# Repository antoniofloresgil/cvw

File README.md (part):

# core-v-wally

This repository is a fork of [openhwgroup/cvw](https://github.com/openhwgroup/cvw) (CORE-V-Wally) that is
more than Wally: next to the processor it holds an [open FPGA flow, an open ASIC flow with a
microcontroller chip, a KiCad test board and FreeRTOS](#what-this-fork-adds). The core and its configurations
are Wally's, upstream is merged into `main` regularly, and every addition to the core is behind a configuration
parameter that is off by default, so the upstream configurations behave as before
([the inventory](docs/engineering/upstream-coupling.md)). The rest of this README is upstream's setup guide
and still applies.

Wally is a 5-stage pipelined processor configurable to support up through the RVA22 profile, including virtual memory, PMP, and the various privileged modes and CSRs. The rv64gc configuration supports:

- RV64IMAFDCB with M, S, and U modes
- Zicsr, Zifencei, Zicntr, Zihpm, Zicond, and Zicclsm
- Zbc
- Zkn scalar crypto (Zbkb, Zbkc, Zbkx, Zknd, Zkne, and Zknh)
- Zcb
- Zfh and Zfa
- Zicbom, Zicboz, and Zicbop
- Sstc
- Sv39, Sv48, and Sv57 virtual memory with Svpbmt, Svnapot, Svinval, and Svadu
- 16 PMP entries

Other configurations range down to a minimal RV32E core, and derivative configurations add the Q extension. Wally provides optional caches, branch prediction, and standard RISC-V peripherals (CLINT, PLIC, UART, GPIO).   Wally is written in SystemVerilog.  It passes the [RISC-V Arch Tests](https://github.com/riscv/riscv-arch-test) and boots Linux on an FPGA.  Wally is part of the OpenHW Foundation family of robust open RISC-V cores.

Wally is described in a textbook, [*RISC-V System-on-Chip Design*](https://pages.hmc.edu/harris/ddca/rvsocd.html), by Harris, Stine, Thompson, and Harris.  Users should follow the setup instructions below.

# What this fork adds

| | What it is | Where |
|---|---|---|
| **Open FPGA flow** | Wally on Xilinx 7-series boards with no Vivado: Yosys, nextpnr-xilinx (openXC7) and Project X-Ray, with LiteX/LiteDRAM for the DDR3 instead of Vivado's MIG. On the Nexys Video the RV32 design runs at 40 MHz and RV64GC boots Linux to a BusyBox shell at 12.5 MHz. The Vivado flow stays. The chip below also builds for the Nexys Video (`make nexysvideochip`). | `fpga/`, [flow and LiteDRAM](docs/fpga-opensource-litedram.md), [DDR3 bring-up](docs/engineering/experiments/open-ddr3-bringup.md), [the chip on the FPGA](docs/fpga-chip.md) |
| **Open ASIC flow** | Wally from RTL to GDS with LibreLane on the IHP SG13G2 and SG13CMOS5L open PDKs, with KLayout and Magic DRC, LVS and timing signoff, all open tools. It builds a chip: **`asic_soc_rv32imac`**, an RV32IMAC RISC-V microcontroller with 16 PMP entries, the JTAG debug port and instruction trace, 64 KiB of SRAM in eight macros, an SPI-flash/UART bootloader, a timer with PWM and capture, a watchdog, I2C, an RTC and a pad ring for a QFN 32. It has not been fabricated. | `asic/librelane/`, [README](asic/librelane/README.md), [ADR 0022](docs/engineering/decisions/0022-asic-microcontroller.md) |
| **Test board** | A KiCad 10 board for that chip: USB-C, an FT2232H for JTAG and UART, SPI flash, I2C and analog parts to try the peripherals, and, in a second variant (rev A-S), a test socket for the QFN 32 chip next to the direct-soldering one (rev A). Its schematic and PCB are generated and routed by Python scripts, and `fab.py` writes the JLCPCB files. `make boardsim` simulates the chip on the board's own netlist. | `hardware/board/`, [README](hardware/board/README.md), [ADR 0023](docs/engineering/decisions/0023-mcu-test-board.md) |
| **Real-time OS** | FreeRTOS and Zephyr run on the chip, with static memory protection from locked PMP entries (FreeRTOS) and User-mode threads isolated by the PMP (Zephyr, with drivers for the UART, GPIO, SPI, PWM, I2C, watchdog, MCU timer with capture and RTC, GPIO and I2C interrupts, and the instruction trace switched on by the kernel); their demos are tested in the chip's RTL simulation (`make chipsim`, 15 tests). | `asic/librelane/chip/freertos/`, `asic/librelane/chip/zephyr/` |
| **Debug and trace** | RISC-V Debug 1.0 over JTAG (halt, step, triggers, System Bus Access; OpenOCD and GDB) and an E-Trace instruction trace. | [debug](docs/debug.md), [trace](docs/trace.md), `testbench/debug/` |
| **Multicore and PMU** | Optional multicore (`NCORES`) with private MSI/MESI caches and Linux SMP; the Sscofpmf, Smcntrpmf and Smcdeleg counter extensions and an SBI PMU. | [engineering notes](docs/engineering/README.md) |

The design decisions, measurements and what is still open are written down in
[`docs/engineering/`](docs/engineering/README.md): architecture decision records, experiment records and
[current work](docs/engineering/current-work.md). To use the fork, clone `antoniofloresgil/cvw` with
`--recurse-submodules` (the step-by-step setup below clones upstream; the commands are the same).

# Configurations

Wally default configurations are listed below.  Synthesis results are from TSMC 28HPC+ TT conditions (0.9 V, 25 °C), Design Compiler Y-2026.03-SP3 physical (topographical) synthesis, with timing that includes its estimated wire delays, before place and route.  The hierarchy is ungrouped automatically, and the clock frequency counts paths into the register files, which are written on the falling edge, as half-cycle paths.  Embench results are without F and D.

|                       | rv32e             | rv32i               | rv32imc                           | rv32imcb                              | rv32gc                                                                                                                                       | rv64i      | rv64gc                                                                                                                                                                    |
| --------------------- | ----------------- | ------------------- | --------------------------------- | ------------------------------------- | -------------------------------------------------------------------------------------------------------------------------------------------- | ---------- | ------------------------------------------------------------------------------------------------------------------------------------------------------------------------- |
| Features              | Tiny Embedded     | RVI20U32            | Microcontroller                   | Microcontroller with bit manipulation | Like rv64gc                                                                                                                                  | RVI20U64   | RVA22S64                                                                                                                                                                  |
| Privilege Modes       | M                 | M                   | M, U                              | M, U                                  | M, S, U                                                                                                                                      | M          | M, S, U                                                                                                                                                                   |
| Extensions            | E                 | I                   | IMC, Zicsr, Zicntr, Zihpm         | IMCB, Zbc, Zicsr, Zicntr, Zihpm       | IMAFDCB, Zbc, Zbkb, Zbkc, Zbkx, Zkn, Zkt, Zfh, Zfa, Zcb, Zicond, Zicbom, Zicboz, Zicbop, Zifencei, Zicntr, Zihpm, Sv32, Svadu, Svinval, Sstc | I          | IMAFDCB, Zbc, Zbkb, Zbkc, Zbkx, Zkn, Zkt, Zfh, Zfa, Zcb, Zicond, Zicbom, Zicboz, Zicbop, Zifencei, Zicntr, Zihpm, Sv39, Sv48, Sv57, Svadu, Svinval, Svnapot, Svpbmt, Sstc |
| Memory                | Bus               | IROM, DTIM          | IROM, DTIM                        | IROM, DTIM                            | 16 KB I$, 16 KB D$                                                                                                                           | IROM, DTIM | 16 KB I$, 16 KB D$                                                                                                                                                        |
| Branch Predictor      | None              | None                | Static (backward taken)           | Static (backward taken)               | 1K gshare, 1K BTB, 16 RAS                                                                                                                    | None       | 1K gshare, 1K BTB, 16 RAS                                                                                                                                                 |
| Peripherals           | No                | No                  | CLINT, PLIC, UART, GPIO, SPI, PWM | CLINT, PLIC, UART, GPIO, SPI, PWM     | CLINT, PLIC, UART, GPIO, SPI, PWM                                                                                                            | No         | CLINT, PLIC, UART, GPIO, SPI, PWM                                                                                                                                         |
| External bus (AHB)    | Yes               | No                  | Yes                               | Yes                                   | Yes                                                                                                                                          | No         | Yes                                                                                                                                                                       |
| CoreMark/MHz          | 0.35              | 1.04                | 3.54                              | 4.06                                  | 4.33                                                                                                                                         | 0.91       | 4.20                                                                                                                                                                      |
| Embench Speed         | 0.20              | 0.63                | 1.58                              | 1.65                                  | 1.70                                                                                                                                         | 0.70       | 2.03                                                                                                                                                                      |
| Clock Frequency (MHz) | 2800              | 2780                | 1880                              | 1890                                  | 920                                                                                                                                          | 2540       | 770                                                                                                                                                                       |
| Total Area (mm^2)     | 0.0058            | 0.0065              | 0.020                             | 0.021                                 | 0.43                                                                                                                                         | 0.016      | 0.48                                                                                                                                                                      |
| Logic Area (mm^2)     | 0.0058            | 0.0065              | 0.020                             | 0.021                                 | 0.11                                                                                                                                         | 0.016      | 0.17                                                                                                                                                                      |
| Flip-Flops            | 573 + 495 latches | 573 + 1,023 latches | 1,792 + 1,023 latches             | 1,801 + 1,023 latches                 | 16,496                                                                                                                                       | 3,026      | 24,416                                                                                                                                                                    |
| Gates                 | 3,650             | 4,495               | 14,583                            | 16,122                                | 89,945                                                                                                                                       | 10,309     | 139,072                                                                                                                                                                   |
| RAM Bits              | 0                 | 0                   | 0                                 | 0                                     | 312,320                                                                                                                                      | 0          | 356,352                                                                                                                                                                   |

CoreMark and Embench (speed-optimized, scored per MHz) are compiled for each configuration's ISA and simulated with Verilator.  With F and D, the compiler optimizes away much of the timed work in the Embench nbody, st, and minver benchmarks, so Embench is compiled without F and D for every configuration, and its floating-point benchmarks use software floating point rather than the FPU.  rv32e, rv32i, and rv64i add performance counters to time the benchmarks.  Synthesis is of `wallypipelinedcore`, with rv32i, rv32imc, rv32imcb, and rv64i using the AHB bus in place of the IROM and DTIM.  The clock frequency is the best of three synthesis targets, and the area is from that run.  Flip-flops and gates are standard cells; gates exclude buffers and inverters.  rv32e, rv32i, rv32imc, and rv32imcb build the integer register file from latches (`LATCH_BASED_REGISTERFILE`), counted separately, including a clock-gate latch for each register.  RAM bits are the SRAM bits used for I$ and D$ data and tags, BTB, and PHT; the SRAM macros take 0.31 mm^2 in rv32gc and rv64gc.

See also [comparison to other cores](docs/comparison.adoc).

# Verification

Wally is presently at Technology Readiness Level 4, passing the [RISC-V architectural certification tests](https://github.com/riscv/riscv-arch-test) and custom tests, and booting Linux in simulation and on an FPGA.  The rv32imc, rv32gc, and rv64gc configurations achieve 100% code and functional coverage.  See the [Test Plan](docs/testplans/testplan.md) for details.

# New User Setup

New users may wish to do the following setup to access the server via a GUI and use a text editor.

- Git started with Git configuration and authentication: C.1  (replace with your name and email)
  ```bash
  $ git config --global user.name "Ben Bitdiddle"
  $ git config --global user.email "ben_bitdiddle@wally.edu"
  $ git config --global pull.rebase false
  ```
- Optional: Download and install x2go - B.1.1
- Optional: Download and install VSCode - B.4.2
- Optional: Make sure you can log into your server via x2go and via a terminal
  - Terminal on Mac, cmd on Windows, xterm on Linux
  - See B.1 about ssh -Y login from a terminal

Then fork and clone the repo, source setup, make the tests and run regression

1. If you don't already have a Github account, create one
2. In a web browser, visit https://github.com/openhwfoundation/cvw
3. In the upper right part of the screen, click on Fork
4. Create a fork, choosing the owner as your github account and the repository as cvw.
5. On the Linux computer where you will be working, log in.
6. Clone your fork of the repo. Change `<yourgithubid>` to your github id.
  ```bash
  $ git clone --recurse-submodules https://github.com/<yourgithubid>/cvw
  $ cd cvw
  $ git remote add upstream https://github.com/openhwfoundation/cvw
  ```

> [!NOTE]
> If you are installing on a new system without any tools installed, please jump to the next section, [Toolchain Installation](#toolchain-installation-and-configuration), then come back here.

7. Run the setup script to set `$WALLY` and `$RISCV` and add `$WALLY/bin` to your `PATH`.

  ```bash
  $ source ./setup.sh
  ```

8. Add the following lines to your `.bashrc` or `.bash_profile` to run the setup script each time you log in.

  ```bash
  if [ -f ~/cvw/setup.sh ]; then
    source ~/cvw/setup.sh
  fi
  ```

9. Try compiling the HelloWally program and simulating it on the SystemVerilog with Verilator and on the Spike simulator.
  ```
  $ cd examples/C/hello
  $ make
  $ wsim --sim verilator rv64gc --elf hello
  Hello Wally!
  0 1 2 3 4 5 6 7 8 9
  $ spike hello
  Hello Wally!
  0 1 2 3 4 5 6 7 8 9
  ```

10. Build the tests from the cvw directory and run a regression simulation to prove everything is installed.  Building tests may take a while.

  ```bash
  $ cd ~/cvw && make --jobs
  $ regression-wally
  ```

# Toolchain Installation and Configuration

This section describes the open source toolchain installation.

### Compatibility
The current version of the toolchain has been tested on Ubuntu (versions 20.04 LTS, 22.04 LTS, 24.04 LTS, and 26.04 LTS), Debian (versions 12 and 13), Red Hat/Rocky/AlmaLinux (versions 8, 9, and 10), SUSE versions 15.6 and 16.0 and Fedora (version 44). Only the latest minor release of each major version is tested.

> [!WARNING]
> - Ubuntu 22.04 LTS is incompatible with Synopsys Design Compiler.
> - Whisper is not installed on Ubuntu 20.04 LTS due to issues compiling the boost libraries.

### Overview
The toolchain installation script installs the following tools:
- [RISC-V GNU Toolchain](https://github.com/riscv-collab/riscv-gnu-toolchain): GCC and accompanying compiler tools
- [QEMU](https://www.qemu.org/docs/master/system/target-riscv.html): emulator
- [Spike](https://github.com/riscv-software-src/riscv-isa-sim): functional RISC-V model
- [Whisper](https://github.com/tenstorrent/whisper): RISC-V instruction set simulator (ISS)
- [Verilator](https://github.com/verilator/verilator): open-source Verilog simulator
- [RISC-V Sail Model](https://github.com/riscv/sail-riscv): golden reference model for RISC-V
- [OSU Skywater 130 cell library](https://foss-eda-tools.googlesource.com/skywater-pdk/libs/sky130_osu_sc_t12): standard cell library
- [uv](https://docs.astral.sh/uv/): Python package manager and virtual environment tool
- [mise](https://mise.jdx.dev/): development environment setup tool for managing tool versions and environment variables
- [Yosys](https://github.com/YosysHQ/yosys) and [yosys-slang](https://github.com/povik/yosys-slang): Verilog/SystemVerilog synthesis
- [nextpnr-xilinx](https://github.com/openXC7/nextpnr-xilinx): placement and routing for Xilinx 7-series FPGAs
- [Project X-Ray](https://github.com/f4pga/prjxray): Xilinx 7-series device database and bitstream tools
- [openFPGALoader](https://github.com/trabucayre/openFPGALoader): FPGA SRAM and flash programmer

The FPGA installation also generates nextpnr chip databases for the `xc7a100t` used by the Arty A7-100T and Nexys A7-100T and the `xc7a200t` used by the Nexys Video. On the Arty A7 and Nexys A7 the open-source flow builds a reduced Wally configuration with internal BRAM, UART, GPIO and CLINT. On the Nexys Video it uses a LiteX/LiteDRAM DDR3 controller instead of Vivado IP, and can build either the reduced RV32 configuration or the RV64GC Linux configuration (`OPENCONFIG=fpganexysvideo`, see [docs/fpga-opensource-litedram.md](docs/fpga-opensource-litedram.md)).

After sourcing `$WALLY/setup.sh`, generate a bitstream with either:

```bash
cd fpga/generator
make FLOW=vivado ArtyA7
make FLOW=vivado nexysa7
make FLOW=vivado nexysvideo
make FLOW=opensource ArtyA7
make FLOW=opensource nexysa7
make FLOW=opensource nexysvideo
```

`make nexysvideochip` (no `FLOW`) builds the microcontroller chip of the ASIC flow for the Nexys Video, with no DDR3 ([docs/fpga-chip.md](docs/fpga-chip.md)). The open-source output is written under `fpga/generator/opensource-<board>/`. The open-source flow is experimental: it targets 25 MHz on the Arty A7-100T and Nexys A7-100T and 40 MHz on the Nexys Video. So far only the Nexys Video bitstream has been programmed on hardware (`DONE=1`); DDR3 bring-up is still in progress (see `docs/fpga-opensource-litedram.md`).

Additionally, Buildroot Linux is built for Wally and linux test-vectors are generated for simulation. See the [Linux README](linux/README.md) for more details. This can be skipped using the `--no-buildroot` flag.

### Installation

The tools can be installed by running this from your `cvw` directory (`$WALLY` is not set until `setup.sh` has been sourced, and `setup.sh` needs the tools installed first)

```bash
$ ./bin/wally-tool-chain-install.sh
```
If this script is run as root or using `sudo`, it will also install all of the prerequisite packages using the system package manager. The default installation directory when run in this manner is `/opt/riscv`.

If a user-level installation is desired, the script can instead be run by any user without `sudo` and the installation directory will be `~/riscv`. In this case, the prerequisite packages must first be installed by running

```bash
$ sudo ./bin/wally-package-install.sh
```

In either case, the installation directory can be overridden by passing the desired directory as an argument to the installation script. For example,

```bash
$ sudo ./bin/wally-tool-chain-install.sh /home/riscv
```

See `wally-tool-chain-install.sh` and the scripts in the `bin/installation` directory for a detailed description of each component, or to issue the commands one at a time to install on the command line.

> [!NOTE]
> The complete installation process requires ~55 GB of free space. If the `--clean` flag is passed to the installation script then the final consumed space is only ~26 GB. The `--clean` flag removes source files and build directories.

### Configuration
`$WALLY/setup.sh` sources `$RISCV/site-setup.sh`. If the toolchain was installed in either of the default locations (`/opt/riscv` or `~/riscv`), `$RISCV` will automatically be set to the correct path when `setup.sh` is run. If a custom installation directory was used, then `$WALLY/setup.sh` must be modified to set the correct path.

`$RISCV/site-setup.sh` allows for customization of the site specific information such as commercial licenses and PATH variables. It is automatically copied into your `$RISCV` folder when the installation script is run.

Change the following lines to point to the path and license server for your Siemens Questa and Synopsys Design Compiler and VCS installations and license servers.  If you only have Questa or VCS, you can still simulate but cannot run logic synthesis.  If Questa, VSC, or Design Compiler are already setup on this system then don't set these variables.

```bash
export MGLS_LICENSE_FILE=..         # Change this to your Siemens license server
export SNPSLMD_LICENSE_FILE=..      # Change this to your Synopsys license server
export QUESTA_HOME=..               # Change this for your path to Questa
export DC_HOME=..                   # Change this for your path to Synopsys Design Compiler
export VCS_HOME=..                  # Change this for your path to Synopsys VCS
```

# Installing EDA Tools

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
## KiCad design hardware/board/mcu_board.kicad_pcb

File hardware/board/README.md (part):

# MCU test board

KiCad 10 project for the test board of `asic_soc_rv32imac`; the decisions are in
`docs/engineering/decisions/0023-mcu-test-board.md`.

The schematic is generated: `mcu_board.py` describes the parts and the net of each pin, and
`kicadgen.py` (standard library only) writes `mcu_board.kicad_sch`, one schematic per sheet (power,
debug, chip, peripherals, fpga), the chip's symbol in `mcu_board.kicad_sym` and `sym-lib-table`.
Edit `mcu_board.py` and regenerate rather than editing the schematics by hand:

    python3 mcu_board.py
    kicad-cli sch erc mcu_board.kicad_sch          # 0 violations expected

Every connected pin gets a short wire and a global label (a power symbol for GND, +5V, +3V3, +1V2,
VBUS), so a net is the set of pins with the same name. The chip's QFN32 pin numbers follow the pad
ring and are provisional until the bonding plan.

The PCB (`mcu_board.kicad_pcb`, 110 x 85 mm, four layers: In1 GND, In2 +3V3) is placed by `mcu_pcb.py`,
which reads the schematic's netlist, loads the footprints, gives the pads their nets, places the parts
by function (`FIXED` positions and `GROUPS` packed beside the part they serve) and writes the design
rules into `mcu_board.kicad_pro`. `route.py` then routes it with Freerouting (2.5.0, run without its GUI):
it first gives every SMD pad of GND and +3V3 a locked via to its plane, exports the board as Specctra DSN,
routes F.Cu and B.Cu, and imports the result. `mcu_board_top.png` and `mcu_board_bottom.png` are KiCad's
3D renders.

    python3 mcu_pcb.py && python3 route.py      # about 5 minutes; regenerating discards the routing

`route.py` routes the USB pair itself first (straight and coupled, both lines 9.28 mm, 0.30 mm tracks
0.20 mm apart: about 90-95 ohm on JLCPCB's JLC04161H-7628 stack-up, an estimate to confirm with their
impedance calculator), joins the connector's second VBUS pair under it, and cleans up what the router
leaves. The router is not deterministic: when a run leaves a connection, run both scripts again.
`mcu_pcb.py --update-values` copies changed values from the schematic onto the routed board.

Routing result: DRC with 0 unconnected items and no electrical violation; the only warnings are the
Pmod footprints' silkscreen outline past the board edge, which the maker clips. The board matches the
schematic.

Manufacturing files (`fab/`, git-ignored):

    python3 fab.py      # Gerbers + drill (zip), BOM and CPL in JLCPCB's columns, schematic and PCB PDFs

U6 (the chip, in a hand-soldered QFN socket), the test points and the mounting holes are not
assembled. The BOM carries LCSC part numbers (the `LCSC` table in `fab.py`, checked against JLCPCB's
catalogue on 2026-11-06): basic parts for the passives and the ferrite, extended parts for the rest;
the through-hole headers and jumpers have none and are soldered by hand.

    python3 mcu_pcb.py                                         # the system Python, which has pcbnew
    kicad-cli pcb drc --refill-zones --schematic-parity mcu_board.kicad_pcb

## The chip's socket: footprint `mcu_board:Yamaichi_IC550-0324-007_QFN32`

The chip (QFN32, 5 x 5 mm, 0.5 mm pitch) will sit in a Yamaichi IC550-0324-007-G test socket, hinged lid, about 92 USD.
`socket_fp.py` writes its footprint, `mcu_board.pretty/Yamaichi_IC550-0324-007_QFN32.kicad_mod`, from Yamaichi's
drawing A111332-001 (`socket_footprint.png` is its picture: `python3 socket_preview.py`). The socket is through-hole:

- 32 holes of 0.5 mm (+0.1/0, drilled 0.55 mm, pads of 0.9 mm) in four groups. A side has 8 contacts at the
  package's 0.5 mm pitch whose tails go to three rows 1 mm apart (squares of 7.5, 9.5 and 11.5 mm): contact k of a side
  is in row k mod 3, so the holes of a row are 1.5 mm apart and the pads are 0.22 mm from each other at the least.
- A ground pin at the centre, hole of 0.8 mm (+0.05/0, drilled 0.85 mm), pad 33, which presses on the package's exposed
  pad. The drawing's note 1 says to mask the centre hole so that solder does not flow into it: the pad has no mask opening.
- Two locating holes of 1.6 mm (+0.1/0, drilled 1.65 mm, not plated) at (+8, +7) and (-8, -7), and five stand-off areas
  (four squares of 5 mm at (+-8.5, +-8.5) and a circle of 2.5 mm at the centre) where the footprint has rule areas
  that keep tracks, vias and pours out of the top copper ("keep the board trace out of area").
- The body is 24.5 x 22 mm, with the hinge on the right: courtyard 11 mm to the left of the package centre, 13.5 mm to the
  right and 11 mm above and below.

The package goes in with its pin 1 at the bottom left corner of the nest (the drawing's pin 1 indicator), which is the
standard drawing turned 90 degrees counter-clockwise: pins 1-8 are on the bottom side from left to right, 9-16 up the
right side, 17-24 along the top from right to left and 25-32 down the left side.

What the drawing does not say, and the footprint assumes: that the tail of the contact under a package pad is at the
same position along its side as the pad (the 0.5 mm steps of the pattern say so, but there is no pin table). Check it
with a multimeter on the first socket (a package pin against the hole of the same number) before ordering several boards.

## Two variants of the board

The same schematic gives two boards, which differ in the footprint of U6 and in the placement around it:

| | `mcu_board.kicad_pcb` (rev A) | `mcu_board_socket.kicad_pcb` (rev A-S) |
|---|---|---|
| The chip | QFN32 soldered directly (pads of 5 x 5 mm) | in the Yamaichi test socket (through-hole, 24.5 x 22 mm body), so it can be changed |
| Make it | `python3 mcu_pcb.py && python3 route.py` | `python3 mcu_pcb.py --socket && python3 route.py --board mcu_board_socket.kicad_pcb` |
| Manufacturing files | `python3 fab.py` into `fab/` | `python3 fab.py --socket` into `fab-socket/` (`mcu_board_socket-*`) |
| Renders | `mcu_board_top.png`, `mcu_board_bottom.png` | `mcu_board_socket_top.png`, `mcu_board_socket_bottom.png` |

Both have 123 assembled parts and the same BOM (U6 is not assembled in either). In the socket variant U6 is turned
270 degrees so that each side of the package faces where it does in rev A (the socket's pin 1 is at the bottom left of its
nest); the decoupling capacitors (C21-C23, C31-C33) are in a row above the body, the oscillator, the clock and reset parts
and the LED buffer are on the bottom side, and the flash and the analogue part moved right to make room. `route.py` also
fans the bottom-side parts out on the bottom copper.

Things that are different in the socket variant, because of its 32 holes 0.5-1.1 mm apart:

- The pads of U6 keep their inner-layer rings only on the layer of their own net, and the planes keep 0.2 mm (not 0.3 mm)
  from them: with 0.3 mm the antipads join and cut the ground pins (12, 29 and 33) off the GND plane. The ground pins
  join the plane with a solid connection.
- The footprint's keep-out areas (the stand-off areas) keep tracks and vias off the top copper under the body's corners.
- Freerouting leaves U11's pad 5 (+3V3) open: a pad of 0.35 mm between a signal and a ground via. This board has a via
  beside it, joined with a 0.15 mm track, put by hand; routing again may need the same.
- `kicad-cli pcb drc --schematic-parity` does not apply (it looks for `mcu_board_socket.kicad_sch`); the nets come from
  the same netlist.
- Routing result, as for rev A: DRC with 0 unconnected items and no electrical violation; the only warnings are the 18 of
  the Pmod footprints' silkscreen past the board edge.

The footprint of the socket, `mcu_board.pretty/Yamaichi_IC550-0324-007_QFN32.kicad_mod`, is described above (and `fp-lib-table`
makes it available to KiCad's editor as `mcu_board`).

`chip_qfn32_socket.png` shows the chip's real layout (final GDS) in the QFN32 with the bonding the
schematic assumes: each pad of the ring to the nearest package pin, one pin free per side.

## Simulation

`sim/` simulates the chip on the board's own netlist (`make boardsim` in `asic/librelane`, or
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
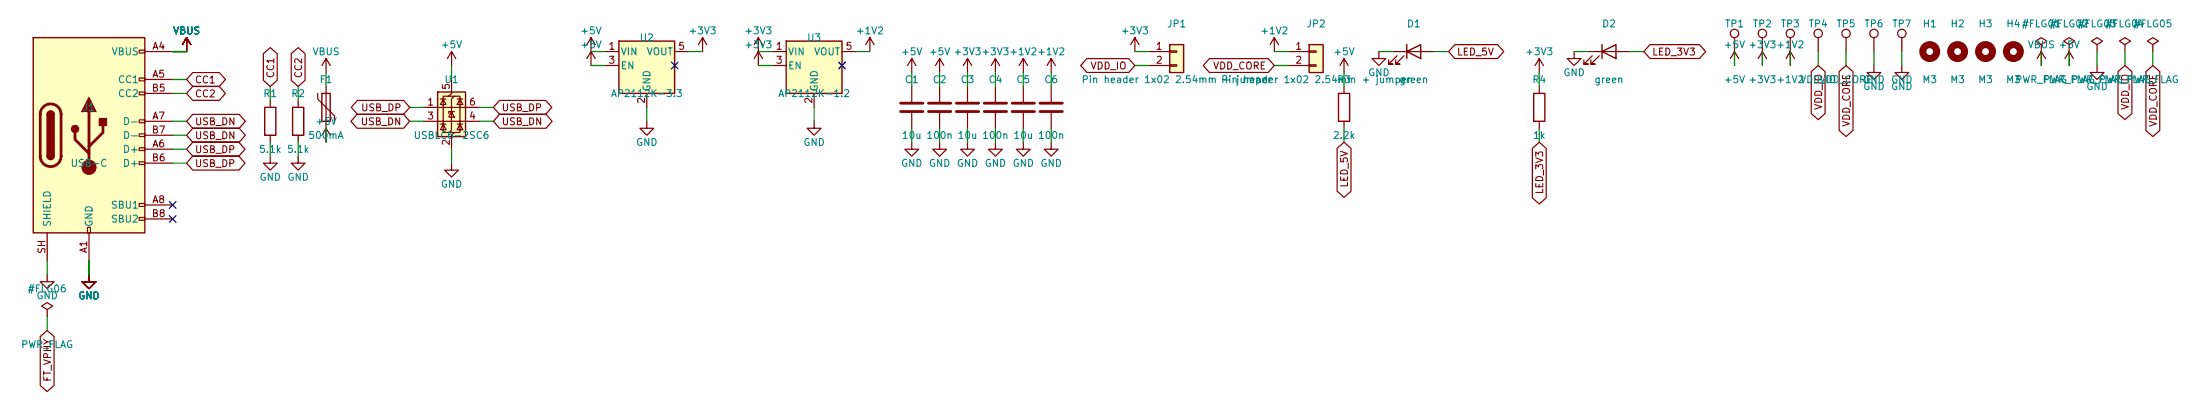
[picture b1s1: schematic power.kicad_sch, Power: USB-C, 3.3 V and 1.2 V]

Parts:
C1, C3, C5: 10u; C_0805_2012Metric
C2, C4, C6: 100n; C_0603_1608Metric
D1, D2: green; LED_0603_1608Metric
F1: 500mA; Fuse_1206_3216Metric
H1, H2, H3, H4: M3; MountingHole_3.2mm_M3
J1: USB-C; USB_C_Receptacle_HRO_TYPE-C-31-M-12
JP1, JP2: Pin header 1x02 2.54mm + jumper; PinHeader_1x02_P2.54mm_Vertical
R1, R2: 5.1k; R_0603_1608Metric
R3: 2.2k; R_0603_1608Metric
R4: 1k; R_0603_1608Metric
TP1: +5V; TestPoint_Pad_D1.5mm
TP2: +3V3; TestPoint_Pad_D1.5mm
TP3: +1V2; TestPoint_Pad_D1.5mm
TP4: VDD_IO; TestPoint_Pad_D1.5mm
TP5: VDD_CORE; TestPoint_Pad_D1.5mm
TP6, TP7: GND; TestPoint_Pad_D1.5mm
U1: USBLC6-2SC6; SOT-23-6
U2: AP2112K-3.3; SOT-23-5
U3: AP2112K-1.2; SOT-23-5

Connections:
+1V2: C5.1, C6.1, JP2.1, TP3.1, U3.5 (VOUT)
+3V3: C3.1, C4.1, JP1.1, R4.1, TP2.1, U2.5 (VOUT), U3.1 (VIN), U3.3 (EN); also elsewhere on the board
+5V: C1.1, C2.1, F1.2, R3.1, TP1.1, U1.5 (VBUS), U2.1 (VIN), U2.3 (EN)
CC1: J1.A5 (CC1), R1.1
CC2: J1.B5 (CC2), R2.1
GND: C1.2, C2.2, C3.2, C4.2, C5.2, C6.2, D1.1 (K), D2.1 (K), J1.A1 (GND), J1.A12 (GND), J1.B1 (GND), J1.B12 (GND), J1.SH (SHIELD), R1.2, R2.2, TP6.1, TP7.1, U1.2 (GND), U2.2 (GND), U3.2 (GND); also elsewhere on the board
LED_3V3: D2.2 (A), R4.2
LED_5V: D1.2 (A), R3.2
USB_DN: J1.A7 (D-), J1.B7 (D-), U1.3 (I/O2), U1.4 (I/O2); also elsewhere on the board
USB_DP: J1.A6 (D+), J1.B6 (D+), U1.1 (I/O1), U1.6 (I/O1); also elsewhere on the board
VBUS: F1.1, J1.A4 (VBUS), J1.A9 (VBUS), J1.B4 (VBUS), J1.B9 (VBUS)
VDD_CORE: JP2.2, TP5.1; also elsewhere on the board
VDD_IO: JP1.2, TP4.1; also elsewhere on the board

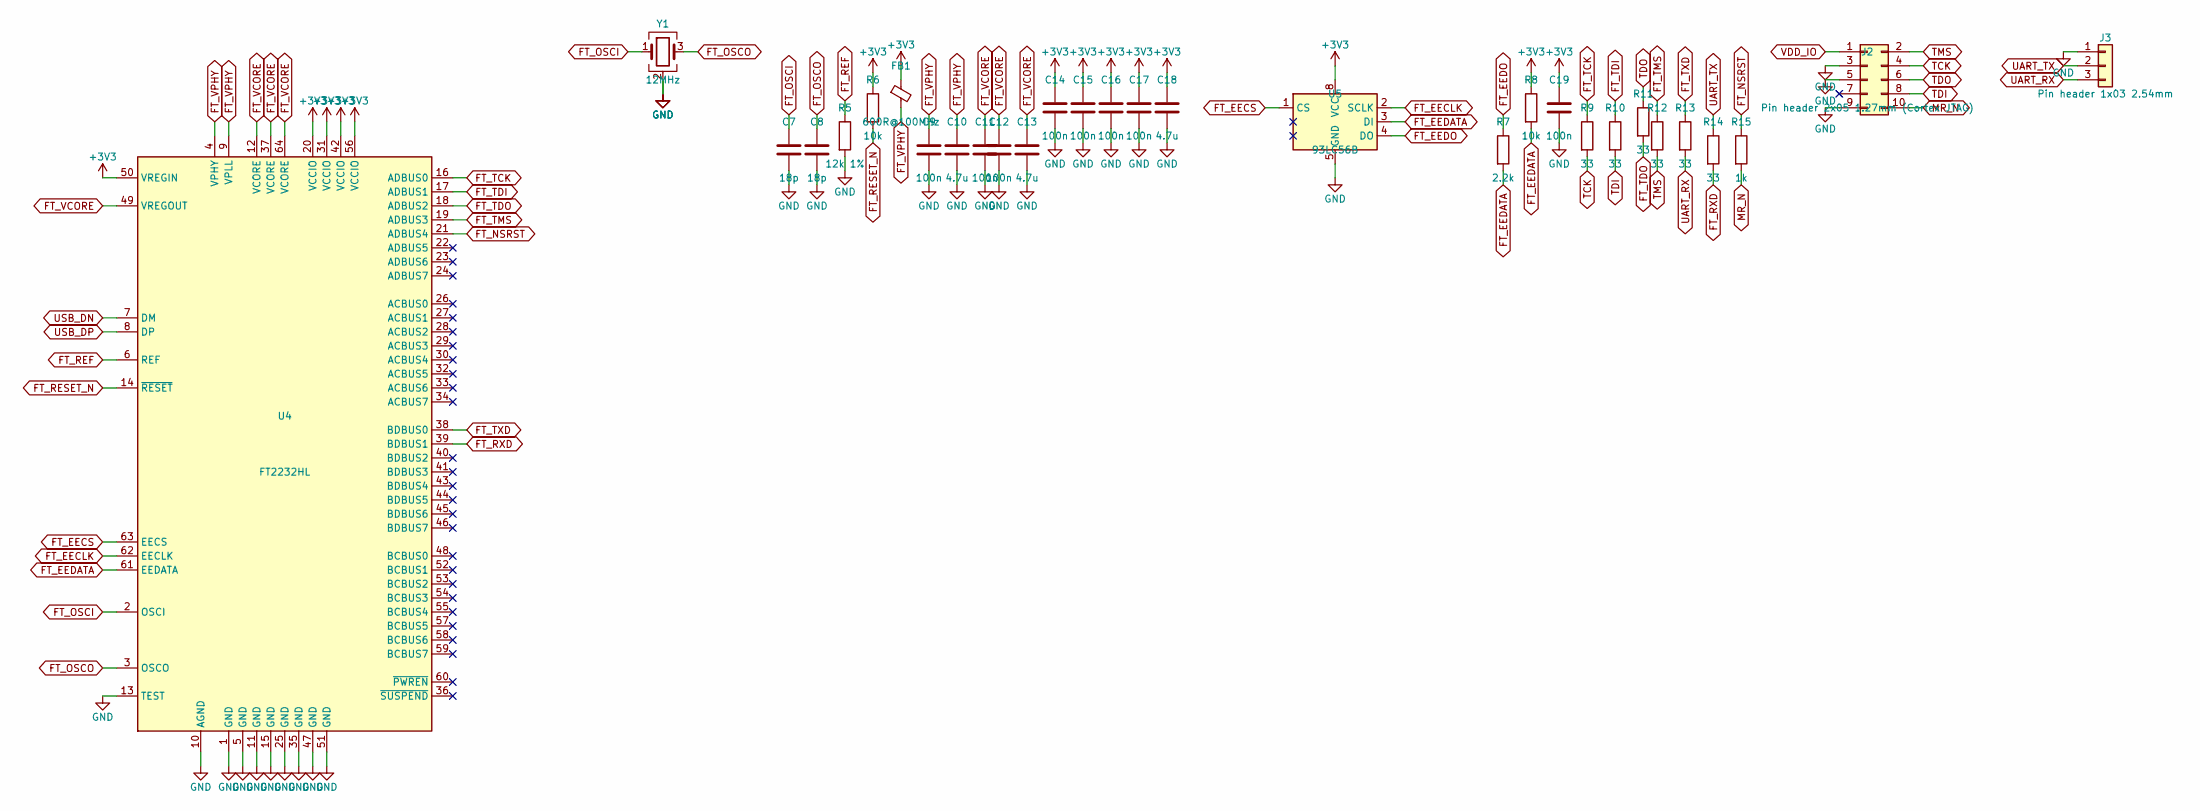
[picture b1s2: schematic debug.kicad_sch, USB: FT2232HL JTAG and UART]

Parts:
C7, C8: 18p; C_0603_1608Metric
C9, C11, C12, C14, C15, C16, C17, C19: 100n; C_0603_1608Metric
C10, C13, C18: 4.7u; C_0805_2012Metric
FB1: 600R@100MHz; L_0603_1608Metric
J2: Pin header 2x05 1.27mm (Cortex JTAG); PinHeader_2x05_P1.27mm_Vertical_SMD
J3: Pin header 1x03 2.54mm; PinHeader_1x03_P2.54mm_Vertical
R5: 12k 1%; R_0603_1608Metric
R6, R8: 10k; R_0603_1608Metric
R7: 2.2k; R_0603_1608Metric
R9, R10, R11, R12, R13, R14: 33; R_0603_1608Metric
R15: 1k; R_0603_1608Metric
U4: FT2232HL; LQFP-64_10x10mm_P0.5mm
U5: 93LC56B; SOIC-8_3.9x4.9mm_P1.27mm
Y1: 12MHz; Crystal_SMD_3225-4Pin_3.2x2.5mm

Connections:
+3V3: C14.1, C15.1, C16.1, C17.1, C18.1, C19.1, FB1.1, R6.1, R8.1, U4.20 (VCCIO), U4.31 (VCCIO), U4.42 (VCCIO), U4.50 (VREGIN), U4.56 (VCCIO), U5.8 (VCC); also elsewhere on the board
FT_EECLK: U4.62 (EECLK), U5.2 (SCLK)
FT_EECS: U4.63 (EECS), U5.1 (CS)
FT_EEDATA: R7.2, R8.2, U4.61 (EEDATA), U5.3 (DI)
FT_EEDO: R7.1, U5.4 (DO)
FT_NSRST: R15.1, U4.21 (ADBUS4)
FT_OSCI: C7.1, U4.2 (OSCI), Y1.1
FT_OSCO: C8.1, U4.3 (OSCO), Y1.3
FT_REF: R5.1, U4.6 (REF)
FT_RESET_N: R6.2, U4.14 (~RESET)
FT_RXD: R14.2, U4.39 (BDBUS1)
FT_TCK: R9.1, U4.16 (ADBUS0)
FT_TDI: R10.1, U4.17 (ADBUS1)
FT_TDO: R11.2, U4.18 (ADBUS2)
FT_TMS: R12.1, U4.19 (ADBUS3)
FT_TXD: R13.1, U4.38 (BDBUS0)
FT_VCORE: C11.1, C12.1, C13.1, U4.12 (VCORE), U4.37 (VCORE), U4.49 (VREGOUT), U4.64 (VCORE)
FT_VPHY: C9.1, C10.1, FB1.2, U4.4 (VPHY), U4.9 (VPLL)
GND: C7.2, C8.2, C9.2, C10.2, C11.2, C12.2, C13.2, C14.2, C15.2, C16.2, C17.2, C18.2, C19.2, J2.3, J2.5, J2.9, J3.1, R5.2, U4.1 (GND), U4.5 (GND), U4.10 (AGND), U4.11 (GND), U4.13 (TEST), U4.15 (GND), U4.25 (GND), U4.35 (GND), U4.47 (GND), U4.51 (GND), U5.5 (GND), Y1.2 (G), Y1.4 (G); also elsewhere on the board
MR_N: J2.10, R15.2; also elsewhere on the board
TCK: J2.4, R9.2; also elsewhere on the board
TDI: J2.8, R10.2; also elsewhere on the board
TDO: J2.6, R11.1; also elsewhere on the board
TMS: J2.2, R12.2; also elsewhere on the board
UART_RX: J3.3, R13.2; also elsewhere on the board
UART_TX: J3.2, R14.1; also elsewhere on the board
USB_DN: U4.7 (DM); also elsewhere on the board
USB_DP: U4.8 (DP); also elsewhere on the board
VDD_IO: J2.1; also elsewhere on the board

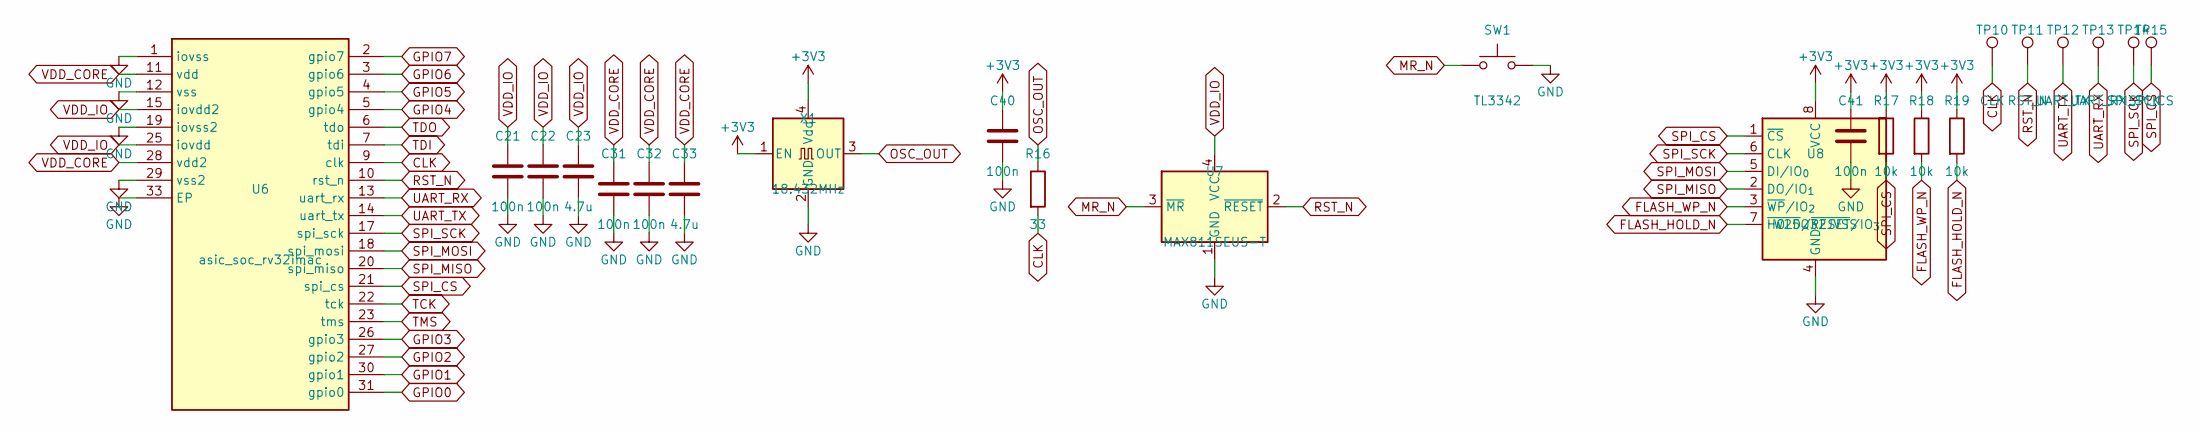
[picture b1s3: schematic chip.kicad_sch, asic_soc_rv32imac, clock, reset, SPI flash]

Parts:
C21, C22, C31, C32, C40, C41: 100n; C_0603_1608Metric
C23, C33: 4.7u; C_0805_2012Metric
R16: 33; R_0603_1608Metric
R17, R18, R19: 10k; R_0603_1608Metric
SW1: TL3342; SW_SPST_TL3342
TP10: CLK; TestPoint_Pad_D1.5mm
TP11: RST_N; TestPoint_Pad_D1.5mm
TP12: UART_TX; TestPoint_Pad_D1.5mm
TP13: UART_RX; TestPoint_Pad_D1.5mm
TP14: SPI_SCK; TestPoint_Pad_D1.5mm
TP15: SPI_CS; TestPoint_Pad_D1.5mm
U6: asic_soc_rv32imac; QFN-32-1EP_5x5mm_P0.5mm_EP3.3x3.3mm
U7: MAX811SEUS-T; SOT-143
U8: W25Q32JVSS; SOIC-8_5.3x5.3mm_P1.27mm
X1: 18.432MHz; Oscillator_SMD_Abracon_ASE-4Pin_3.2x2.5mm

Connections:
+3V3: C40.1, C41.1, R17.1, R18.1, R19.1, U8.8 (VCC), X1.1 (EN), X1.4 (Vdd); also elsewhere on the board
CLK: R16.2, TP10.1, U6.9 (clk); also elsewhere on the board
FLASH_HOLD_N: R19.2, U8.7 (~HOLD/~RESET/IO_{3})
FLASH_WP_N: R18.2, U8.3 (~WP/IO_{2})
GND: C21.2, C22.2, C23.2, C31.2, C32.2, C33.2, C40.2, C41.2, SW1.2, U6.1 (iovss), U6.12 (vss), U6.19 (iovss2), U6.29 (vss2), U6.33 (EP), U7.1 (GND), U8.4 (GND), X1.2 (GND); also elsewhere on the board
GPIO0: U6.31 (gpio0); also elsewhere on the board
GPIO1: U6.30 (gpio1); also elsewhere on the board
GPIO2: U6.27 (gpio2); also elsewhere on the board
GPIO3: U6.26 (gpio3); also elsewhere on the board
GPIO4: U6.5 (gpio4); also elsewhere on the board
GPIO5: U6.4 (gpio5); also elsewhere on the board
GPIO6: U6.3 (gpio6); also elsewhere on the board
GPIO7: U6.2 (gpio7); also elsewhere on the board
MR_N: SW1.1, U7.3 (~MR); also elsewhere on the board
OSC_OUT: R16.1, X1.3 (OUT)
RST_N: TP11.1, U6.10 (rst_n), U7.2 (~RESET); also elsewhere on the board
SPI_CS: R17.2, TP15.1, U6.21 (spi_cs), U8.1 (~CS); also elsewhere on the board
SPI_MISO: U6.20 (spi_miso), U8.2 (DO/IO_{1}); also elsewhere on the board
SPI_MOSI: U6.18 (spi_mosi), U8.5 (DI/IO_{0}); also elsewhere on the board
SPI_SCK: TP14.1, U6.17 (spi_sck), U8.6 (CLK); also elsewhere on the board
TCK: U6.22 (tck); also elsewhere on the board
TDI: U6.7 (tdi); also elsewhere on the board
TDO: U6.6 (tdo); also elsewhere on the board
TMS: U6.23 (tms); also elsewhere on the board
UART_RX: TP13.1, U6.13 (uart_rx); also elsewhere on the board
UART_TX: TP12.1, U6.14 (uart_tx); also elsewhere on the board
VDD_CORE: C31.1, C32.1, C33.1, U6.11 (vdd), U6.28 (vdd2); also elsewhere on the board
VDD_IO: C21.1, C22.1, C23.1, U6.15 (iovdd2), U6.25 (iovdd), U7.4 (VCC); also elsewhere on the board

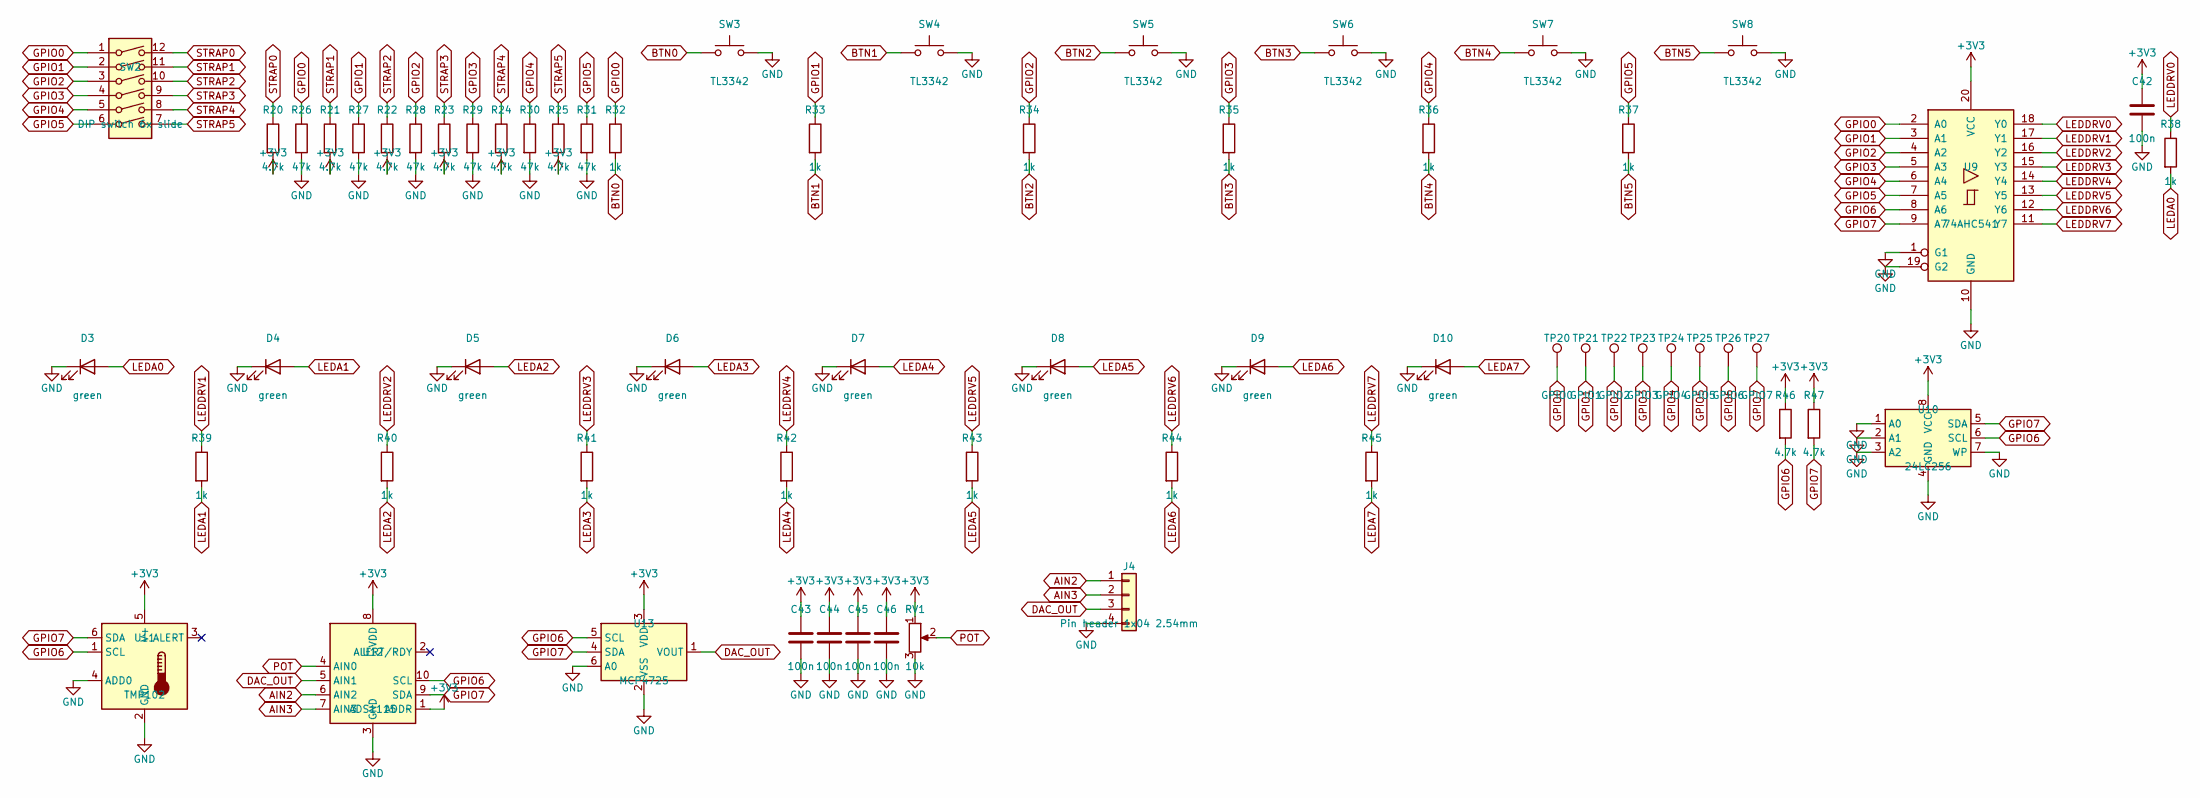
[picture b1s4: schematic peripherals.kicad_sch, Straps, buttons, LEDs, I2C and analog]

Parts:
C42, C43, C44, C45, C46: 100n; C_0603_1608Metric
D3, D4, D5, D6, D7, D8, D9, D10: green; LED_0603_1608Metric
J4: Pin header 1x04 2.54mm; PinHeader_1x04_P2.54mm_Vertical
R20, R21, R22, R23, R24, R25, R46, R47: 4.7k; R_0603_1608Metric
R26, R27, R28, R29, R30, R31: 47k; R_0603_1608Metric
R32, R33, R34, R35, R36, R37, R38, R39, R40, R41, R42, R43, R44, R45: 1k; R_0603_1608Metric
RV1: 10k; Potentiometer_Bourns_3314J_Vertical
SW2: DIP switch 6x slide; SW_DIP_SPSTx06_Slide_6.7x16.8mm_W8.61mm_P2.54mm_LowProfile
SW3, SW4, SW5, SW6, SW7, SW8: TL3342; SW_SPST_TL3342
TP20: GPIO0; TestPoint_Pad_D1.5mm
TP21: GPIO1; TestPoint_Pad_D1.5mm
TP22: GPIO2; TestPoint_Pad_D1.5mm
TP23: GPIO3; TestPoint_Pad_D1.5mm
TP24: GPIO4; TestPoint_Pad_D1.5mm
TP25: GPIO5; TestPoint_Pad_D1.5mm
TP26: GPIO6; TestPoint_Pad_D1.5mm
TP27: GPIO7; TestPoint_Pad_D1.5mm
U9: 74AHC541; TSSOP-20_4.4x6.5mm_P0.65mm
U10: 24LC256; SOIC-8_3.9x4.9mm_P1.27mm
U11: TMP102; SOT-563
U12: ADS1115; TSSOP-10_3x3mm_P0.5mm
U13: MCP4725; SOT-23-6

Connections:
+3V3: C42.1, C43.1, C44.1, C45.1, C46.1, R20.2, R21.2, R22.2, R23.2, R24.2, R25.2, R46.1, R47.1, RV1.1, U9.20 (VCC), U10.8 (VCC), U11.5 (V+), U12.1 (ADDR), U12.8 (VDD), U13.3 (VDD); also elsewhere on the board
AIN2: J4.1, U12.6 (AIN2)
AIN3: J4.2, U12.7 (AIN3)
BTN0: R32.2, SW3.1
BTN1: R33.2, SW4.1
BTN2: R34.2, SW5.1
BTN3: R35.2, SW6.1
BTN4: R36.2, SW7.1
BTN5: R37.2, SW8.1
DAC_OUT: J4.3, U12.5 (AIN1), U13.1 (VOUT)
GND: C42.2, C43.2, C44.2, C45.2, C46.2, D3.1 (K), D4.1 (K), D5.1 (K), D6.1 (K), D7.1 (K), D8.1 (K), D9.1 (K), D10.1 (K), J4.4, R26.2, R27.2, R28.2, R29.2, R30.2, R31.2, RV1.3, SW3.2, SW4.2, SW5.2, SW6.2, SW7.2, SW8.2, U9.1 (G1), U9.10 (GND), U9.19 (G2), U10.1 (A0), U10.2 (A1), U10.3 (A2), U10.4 (GND), U10.7 (WP), U11.2 (GND), U11.4 (ADD0), U12.3 (GND), U13.2 (VSS), U13.6 (A0); also elsewhere on the board
GPIO0: R26.1, R32.1, SW2.1, TP20.1, U9.2 (A0); also elsewhere on the board
GPIO1: R27.1, R33.1, SW2.2, TP21.1, U9.3 (A1); also elsewhere on the board
GPIO2: R28.1, R34.1, SW2.3, TP22.1, U9.4 (A2); also elsewhere on the board
GPIO3: R29.1, R35.1, SW2.4, TP23.1, U9.5 (A3); also elsewhere on the board
GPIO4: R30.1, R36.1, SW2.5, TP24.1, U9.6 (A4); also elsewhere on the board
GPIO5: R31.1, R37.1, SW2.6, TP25.1, U9.7 (A5); also elsewhere on the board
GPIO6: R46.2, TP26.1, U9.8 (A6), U10.6 (SCL), U11.1 (SCL), U12.10 (SCL), U13.5 (SCL); also elsewhere on the board
GPIO7: R47.2, TP27.1, U9.9 (A7), U10.5 (SDA), U11.6 (SDA), U12.9 (SDA), U13.4 (SDA); also elsewhere on the board
LEDA0: D3.2 (A), R38.2
LEDA1: D4.2 (A), R39.2
LEDA2: D5.2 (A), R40.2
LEDA3: D6.2 (A), R41.2
LEDA4: D7.2 (A), R42.2
LEDA5: D8.2 (A), R43.2
LEDA6: D9.2 (A), R44.2
LEDA7: D10.2 (A), R45.2
LEDDRV0: R38.1, U9.18 (Y0)
LEDDRV1: R39.1, U9.17 (Y1)
LEDDRV2: R40.1, U9.16 (Y2)
LEDDRV3: R41.1, U9.15 (Y3)
LEDDRV4: R42.1, U9.14 (Y4)
LEDDRV5: R43.1, U9.13 (Y5)
LEDDRV6: R44.1, U9.12 (Y6)
LEDDRV7: R45.1, U9.11 (Y7)
POT: RV1.2, U12.4 (AIN0)
STRAP0: R20.1, SW2.12
STRAP1: R21.1, SW2.11
STRAP2: R22.1, SW2.10
STRAP3: R23.1, SW2.9
STRAP4: R24.1, SW2.8
STRAP5: R25.1, SW2.7

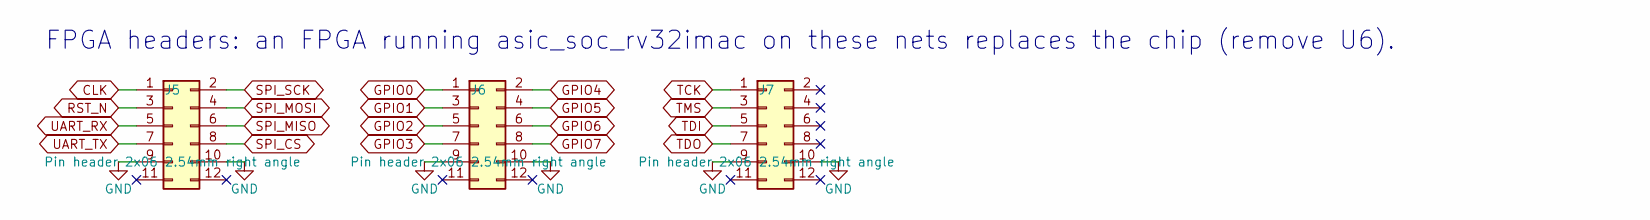
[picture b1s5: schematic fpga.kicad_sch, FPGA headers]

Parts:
J5, J6, J7: Pin header 2x06 2.54mm right angle; PinHeader_2x06_P2.54mm_Horizontal

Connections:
CLK: J5.1; also elsewhere on the board
GND: J5.9, J5.10, J6.9, J6.10, J7.9, J7.10; also elsewhere on the board
GPIO0: J6.1; also elsewhere on the board
GPIO1: J6.3; also elsewhere on the board
GPIO2: J6.5; also elsewhere on the board
GPIO3: J6.7; also elsewhere on the board
GPIO4: J6.2; also elsewhere on the board
GPIO5: J6.4; also elsewhere on the board
GPIO6: J6.6; also elsewhere on the board
GPIO7: J6.8; also elsewhere on the board
RST_N: J5.3; also elsewhere on the board
SPI_CS: J5.8; also elsewhere on the board
SPI_MISO: J5.6; also elsewhere on the board
SPI_MOSI: J5.4; also elsewhere on the board
SPI_SCK: J5.2; also elsewhere on the board
TCK: J7.1; also elsewhere on the board
TDI: J7.5; also elsewhere on the board
TDO: J7.7; also elsewhere on the board
TMS: J7.3; also elsewhere on the board
UART_RX: J5.5; also elsewhere on the board
UART_TX: J5.7; also elsewhere on the board

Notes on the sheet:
FPGA headers: an FPGA running asic_soc_rv32imac on these nets replaces the chip (remove U6).

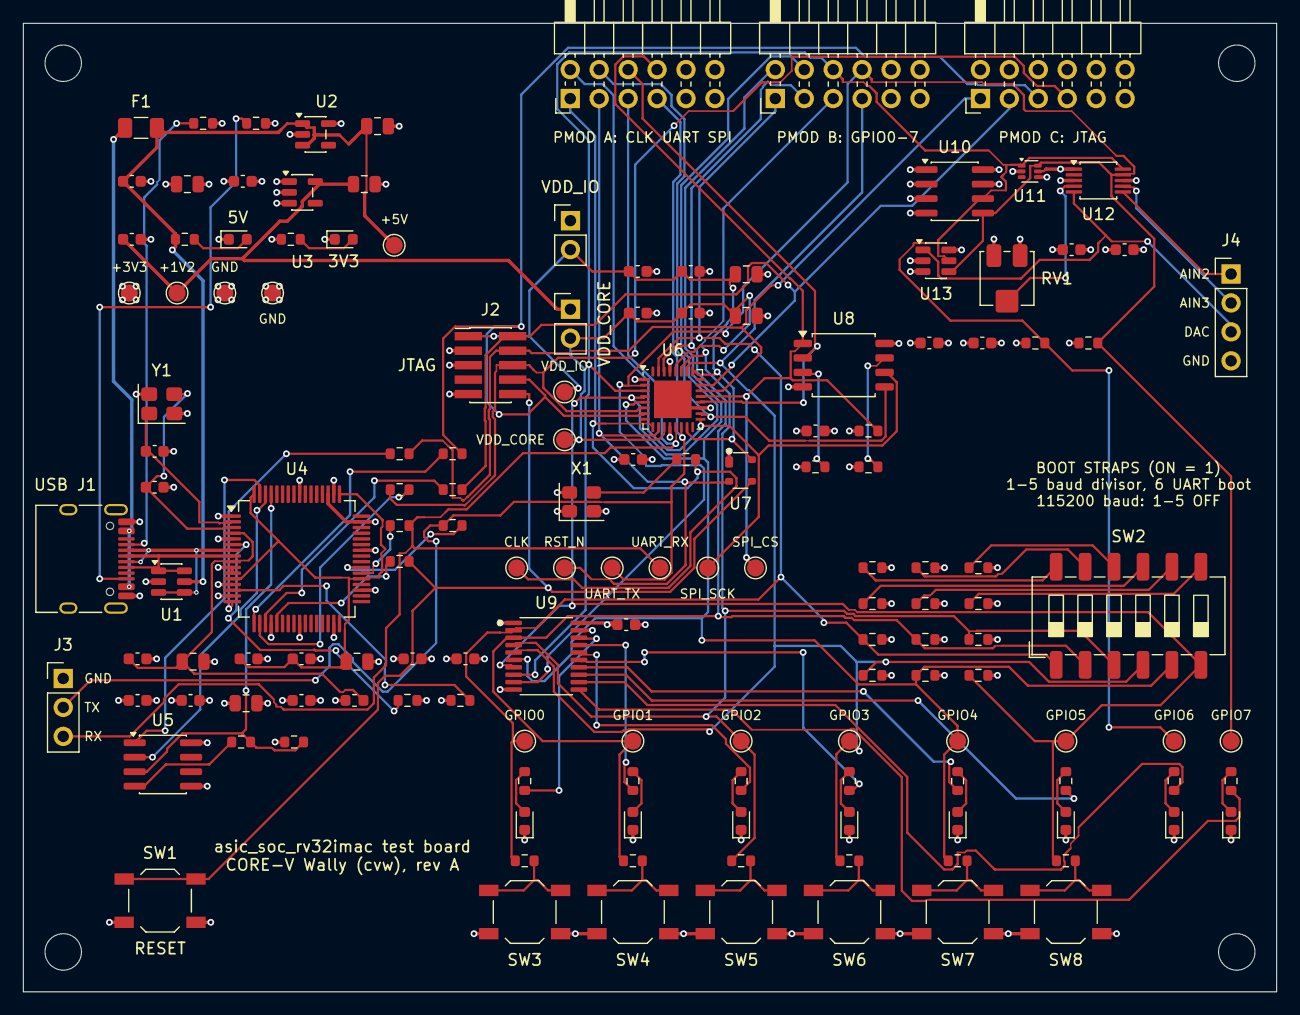
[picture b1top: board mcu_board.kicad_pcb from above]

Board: 4 copper layers, 110.0 x 85.0 mm, 149 parts (0 on the bottom side), 86 nets.

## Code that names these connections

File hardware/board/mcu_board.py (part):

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place before the silicon exists (with the chip removed).  The FT2232HL gives JTAG (channel A, with
nSRST on ADBUS4) and the UART (channel B) on the USB-C.

GPIO: straps GPIO0-5 at reset (boot.S: baud divisor GPIO[4:0], UART-only boot GPIO[5]), set by
DIP switches against 47k pull-downs; timer channels 0-3 on GPIO0-3; I2C on GPIO6-7 with 4.7k
pull-ups.  The LEDs hang off a buffer and the buttons pull through 1k, so neither disturbs a strap
or a peripheral.
"""
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# The chip's QFN32 pinout (provisional until the bonding plan): each pad of the ring goes to the nearest
# package pin, from the pads' places in the final DEF; the eighth pin of each side is not bonded.
# Pins counter-clockwise from pin 1 at the top of the left side (chip_qfn32_socket.png).
RING = [["iovss", "gpio7", "gpio6", "gpio5", "gpio4", "tdo", "tdi"],          # 1-7: west pads, top to bottom
        ["clk", "rst_n", "vdd", "vss", "uart_rx", "uart_tx", "iovdd2"],        # 9-15: south pads, west to east
        ["spi_sck", "spi_mosi", "iovss2", "spi_miso", "spi_cs", "tck", "tms"],  # 17-23: east pads, south to north
        ["iovdd", "gpio3", "gpio2", "vdd2", "vss2", "gpio1", "gpio0"]]          # 25-31: north pads, east to west
PAD_NET = {"clk": "CLK", "rst_n": "RST_N", "uart_rx": "UART_RX", "uart_tx": "UART_TX", "spi_sck": "SPI_SCK",
           "spi_mosi": "SPI_MOSI", "spi_miso": "SPI_MISO", "spi_cs": "SPI_CS", "tck": "TCK", "tms": "TMS",
           "tdi": "TDI", "tdo": "TDO", "vdd": "VDD_CORE", "vdd2": "VDD_CORE", "vss": "GND", "vss2": "GND",
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    s.add("Device", "R", "R15", "1k", {"1": "FT_NSRST", "2": "MR_N"}, footprint=R0603)
    s.add("Connector_Generic", "Conn_02x05_Odd_Even", "J2", "Pin header 2x05 1.27mm (Cortex JTAG)",
          {"1": "VDD_IO", "2": "TMS", "3": "GND", "4": "TCK", "5": "GND", "6": "TDO", "7": "NC", "8": "TDI",
           "9": "GND", "10": "MR_N"}, footprint="Connector_PinHeader_1.27mm:PinHeader_2x05_P1.27mm_Vertical_SMD")
    s.add("Connector_Generic", "Conn_01x03", "J3", "Pin header 1x03 2.54mm", {"1": "GND", "2": "UART_TX", "3": "UART_RX"},
          footprint="Connector_PinHeader_2.54mm:PinHeader_1x03_P2.54mm_Vertical")


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

def peripherals(s):
    # Straps: a DIP switch pulls GPIO0-5 up through 4.7k against a 47k pull-down (open: 0)
    s.add("Switch", "SW_DIP_x06", "SW2", "DIP switch 6x slide",
          {**{str(i + 1): f"GPIO{i}" for i in range(6)}, **{str(12 - i): f"STRAP{i}" for i in range(6)}},
          footprint="Button_Switch_SMD:SW_DIP_SPSTx06_Slide_6.7x16.8mm_W8.61mm_P2.54mm_LowProfile")
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        s.add("Device", "LED", f"D{3 + i}", "green", {"A": f"LEDA{i}", "K": "GND"}, footprint=LED0603)
    for i in range(8):
        s.add("Connector", "TestPoint", f"TP{20 + i}", f"GPIO{i}", {"1": f"GPIO{i}"}, footprint=TP, bom=False)
    # I2C on GPIO6 (SCL) and GPIO7 (SDA): EEPROM 0x50, TMP102 0x48, ADS1115 0x49, MCP4725 0x60
    s.add("Device", "R", "R46", "4.7k", {"1": "+3V3", "2": "GPIO6"}, footprint=R0603)
    s.add("Device", "R", "R47", "4.7k", {"1": "+3V3", "2": "GPIO7"}, footprint=R0603)
    s.add("Memory_EEPROM", "24LC256", "U10", "24LC256", {"A0": "GND", "A1": "GND", "A2": "GND", "GND": "GND",
                                                        "SDA": "GPIO7", "SCL": "GPIO6", "WP": "GND", "VCC": "+3V3"},
          footprint="Package_SO:SOIC-8_3.9x4.9mm_P1.27mm")
    s.add("Sensor_Temperature", "TMP102xxDRL", "U11", "TMP102", {"SCL": "GPIO6", "SDA": "GPIO7", "GND": "GND",
                                                                 "ALERT": "NC", "ADD0": "GND", "V+": "+3V3"})
    s.add("Analog_ADC", "ADS1115IDGS", "U12", "ADS1115", {"ADDR": "+3V3", "ALERT/RDY": "NC", "GND": "GND",
                                                         "AIN0": "POT", "AIN1": "DAC_OUT", "AIN2": "AIN2",
                                                         "AIN3": "AIN3", "VDD": "+3V3", "SDA": "GPIO7", "SCL": "GPIO6"})
    s.add("Analog_DAC", "MCP4725xxx-xCH", "U13", "MCP4725", {"VOUT": "DAC_OUT", "VSS": "GND", "VDD": "+3V3",
                                                             "SDA": "GPIO7", "SCL": "GPIO6", "A0": "GND"})
    for i in range(4):
        s.add("Device", "C", f"C{43 + i}", "100n", {"1": "+3V3", "2": "GND"}, footprint=C0603)
    s.add("Device", "R_Potentiometer", "RV1", "10k", {"1": "+3V3", "2": "POT", "3": "GND"},
          footprint="Potentiometer_SMD:Potentiometer_Bourns_3314J_Vertical")
    s.add("Connector_Generic", "Conn_01x04", "J4", "Pin header 1x04 2.54mm", {"1": "AIN2", "2": "AIN3", "3": "DAC_OUT", "4": "GND"},
          footprint="Connector_PinHeader_2.54mm:PinHeader_1x04_P2.54mm_Vertical")


def fpga(s):
    # Pmod pinout: 1-4 and 7-10 signals, 5 and 11 GND, 6 and 12 VCC (left open: the FPGA board has its own 3.3 V)
    groups = [("J5", "Pin header 2x06 2.54mm right angle", ["CLK", "RST_N", "UART_RX", "UART_TX", "SPI_SCK", "SPI_MOSI", "SPI_MISO", "SPI_CS"]),
              ("J6", "Pin header 2x06 2.54mm right angle", [f"GPIO{i}" for i in range(8)]),
              ("J7", "Pin header 2x06 2.54mm right angle", ["TCK", "TMS", "TDI", "TDO", "NC", "NC", "NC", "NC"])]
    # The header's pads alternate between the rows (1 and 2 face each other): Pmod pin n of the top row
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

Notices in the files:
hardware/board/mcu_board.py:
SPDX-License-Identifier: Apache-2.0 WITH SHL-2.1
